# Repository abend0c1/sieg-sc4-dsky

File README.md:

# SIEG SC4 Display and Keyboard (DSKY) Alternative

This is a replacement Printed Circuit Board (PCB) for the original Sieg SC4 lathe's
control panel. 

The intent is to replace the flat touch panel
buttons with regular illuminated push button switches that
are easier to use when the machine is in operation.

To do that, the original PCB must be removed as it gets in 
the way of the new panel switches. The LCD module on the
original PCB is retained by physically cutting it off 
with a utility knife and mounting it behind a new aluminium panel with a few
bolts and some J-B Weld epoxy.

The original panel looks like:

The new panel has illuminated push button switches arranged
in a more intuitive way:

The connections that were made between the switches on the old PCB
are now made directly between the new switches using hookup wire.

The new PCB is considerably smaller because it does not
have to accommodate the old tactile switches. It can be
connected to the both LCD and switches using ribbon cable.

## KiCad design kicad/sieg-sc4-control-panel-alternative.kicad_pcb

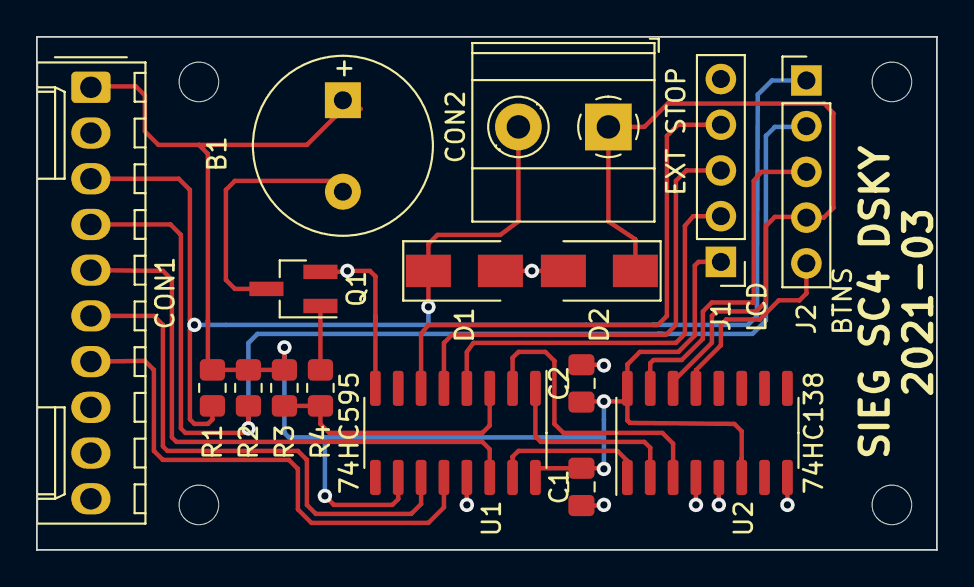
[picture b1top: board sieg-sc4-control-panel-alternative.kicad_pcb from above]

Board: 2 copper layers, 50.0 x 28.5 mm, 20 parts (0 on the bottom side), 19 nets.

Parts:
B1: AX-1005-LF; Buzzer_9.6x5_P5
C1, C2: 100n; C_0805_2012Metric_Pad1.18x1.45mm_HandSolder
CON1: MAIN; Molex_KK-254_AE-6410-10A_1x10_P2.54mm_Vertical
CON2: EXT STOP; TerminalBlock_Phoenix_MKDS-1,5-2_1x02_P5.00mm_Horizontal
D1, D2: SS14; D_SMA
H1, H2, H3, H4: MountingHole; MountingHole_2.2mm_M2
J1: LCD; PinHeader_1x05_P2.54mm_Vertical
J2: BTNS; PinHeader_1x05_P2.54mm_Vertical
Q1: PN2222A; SOT-23_Handsoldering
R1, R2, R3: 4k7; R_0805_2012Metric_Pad1.20x1.40mm_HandSolder
R4: 1k; R_0805_2012Metric_Pad1.20x1.40mm_HandSolder
U1: 74HC595; SOIC-16_3.9x9.9mm_P1.27mm
U2: 74HC138; SOIC-16_3.9x9.9mm_P1.27mm

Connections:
BUZZER: R3.1, R4.2, U1.3
COL1: CON1.4, J2.2, R2.1
COL2: CON1.3, CON2.2, D1.1, J2.1, R1.1
D0: J1.2, U1.4
D1: J1.3, U1.5
D2: J1.4, U1.6
GND: C1.2, C2.2, CON1.2, D1.2, D2.2, J1.5, Q1.2, U1.8, U1.13, U2.4, U2.5, U2.8
LATCH: CON1.7, U1.12
unnamed: B1.2, Q1.3
unnamed: Q1.1, R4.1
unnamed: U1.1, U2.2
unnamed: U1.2, U2.3
unnamed: U1.15, U2.1
ROW1: J2.3, U2.15
ROW2: CON2.1, D2.1, J2.4, U2.14
ROW3: J2.5, U2.13
SCK: CON1.6, U1.11
SDA: CON1.5, U1.14
VCC: B1.1, C1.1, C2.1, CON1.1, J1.1, R1.2, R2.2, R3.2, U1.10, U1.16, U2.6, U2.16

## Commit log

2021-03-31 Removed *bak files from repository
2021-03-31 Moved heading to the top in README.md
